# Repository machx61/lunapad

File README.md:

# lunapad
i made this macropad because well my desk was too empty and i needed something(also out of boredom). it can be mainly used to control music and scroll through pages?(or whatever you may like)

# Features:
- 3x3 matrix: 9 keys to handle the best of your tasks
- Rotary encoder: do stuff with just a twist.
- 14 SK6812 Mini LEDs
- QMK firmware

# Renders

# Working:
- It utilises SEEED XIAORP2040 and a custom designed PCB with custom designed 3d printed enclosure and stuff.
- The macropad runs on QMK firmware and the programmed keys can be changed easily using the source files.

# Assembly:
- the case is split into two parts- top and bottom, held together by 4 M3 screws from the underside. there are also 4 M3x3mm heatset inserts on the topside standoffs. the pcb is sandwiched between the parts.

the screwholes can be seen in the image.

# Bill of Materials

| Part | Quantity | Link |
|:-----|--------:|:------|
| Seeed XIAO RP2040 | 1 | [XIAO](https://robocraze.com/products/seeed-studio-xiao-rp2040-development-board?variant=47742255562976&country=IN&currency=INR&utm_medium=product_sync&utm_source=google&utm_content=sag_organic&utm_campaign=sag_organic&campaignid=23145906364&adgroupid=182236965810&keyword=&device=c&gad_source=1&gad_campaignid=23145906364&gbraid=0AAAAADgHQvYtYGwxuRugn9Vvs_5Luixta&gclid=CjwKCAjw2aPVBhBkEiwA0Cptt0xo3sHi-IdjsARB6GH6TKfZ1M9eswIn35SV6bqsJBOXxCKbRXXIgBoC-xAQAvD_BwE)
| MX-style Mechanical Switch | 9 | [switch](https://neomacro.in/products/cherry-mx-switches?srsltid=AfmBOor8tow3bfeM9PI4JXjRf0VAG1diVYeQj8hqUGDjs-gqPkzoR4SC)
| 1N4148 Diode | 9 | [diode](https://www.ktron.in/product/diode-1n4148-th/?srsltid=AfmBOooRQUjsKqpK_EiK3c9zfrjn3DoaM1cKq1ImvCJTQZmOqeq-VMQ6)
| EC11 Rotary Encoder | 1 | [encoder](https://robu.in/product/rotary-encoder-module/)
| SK6812MINI Addressable RGB LED | 9 | [led](https://www.desertcart.in/products/824340559-50-%E5%80%8B-sk6812-mini-e-rgb-2812b-%E3%81%A8%E5%90%8C%E6%A7%98-sk6812-3228?gad_source=1&gad_campaignid=23077216304&gbraid=0AAAAACnLYYvNHCZW8H4DWDfVWvF8gxS9Q&gclid=CjwKCAjw2aPVBhBkEiwA0Cptt4Ja3nVrBJ97lmX0pUguF7jc3NVgRkxuFrKZ9N5f6J9Q7V-lYQpT1RoC440QAvD_BwE)
| Custom PCB | 1 |
| M3 × 3 mm Brass Heat-Set Insert | 4 | [insert](https://onlyscrews.in/products/m3-x-3mm-brass-threaded-inserts?currency=INR&country=IN&variant=49729062273337&stkn=6e84ebfba1b8&utm_source=google&utm_medium=cpc&utm_campaign=googleads_23949204632&utm_id=23949204632&utm_adgroup=&utm_assetgroup=6722775387&utm_content=ad_&utm_term=&utm_matchtype=&utm_device=c&utm_network=x&gad_source=1&gad_campaignid=23953886635&gbraid=0AAAAA9sP2SRjj_2bfcZD9uxIjMuaLaIao&gclid=CjwKCAjw2aPVBhBkEiwA0Cptt7qy5Bg6gMEtFvCYIa8UhckvOcrG2VIVSBWy-0QVkHM6xJ50sQYSwRoCiMsQAvD_BwE)
| M3 × 12 mm Screw | 4 | [screw](https://onlyscrews.in/products/m3-x-12mm-hex-allen-socket-head-high-tensile12-9-black-anodized-screw?currency=INR&country=IN&variant=49862396903737&stkn=6e84ebfba1b8&utm_source=google&utm_medium=cpc&utm_campaign=googleads_22229903987&utm_id=22229903987&utm_adgroup=&utm_assetgroup=6553248255&utm_content=ad_&utm_term=&utm_matchtype=&utm_device=c&utm_network=x&gad_source=1&gad_campaignid=22229905346&gbraid=0AAAAA9sP2SRGRPWr5iqQc1qZ9YGRh8i3g&gclid=CjwKCAjw2aPVBhBkEiwA0CpttxG6n4pTu_Hwbiq8nsTTyXZsGK1pGMrzw8ansKFSEFKX_LcLPL4uwRoC4dcQAvD_BwE)
| MX Keycap | 9 | [keycap](https://keebmaker.com/products/1u-ymdk-mx-keycaps?variant=49717255012651)
| 3D-Printed Encoder Knob | 1 |
| 3D-Printed Case Top | 1 |
| 3D-Printed Case Bottom | 1 |

# Missing Stuff
- VIA support(i intend to roll it out sometime after)
- an OLED screen(if youd want)
- nothing else for a 3x3 macropad

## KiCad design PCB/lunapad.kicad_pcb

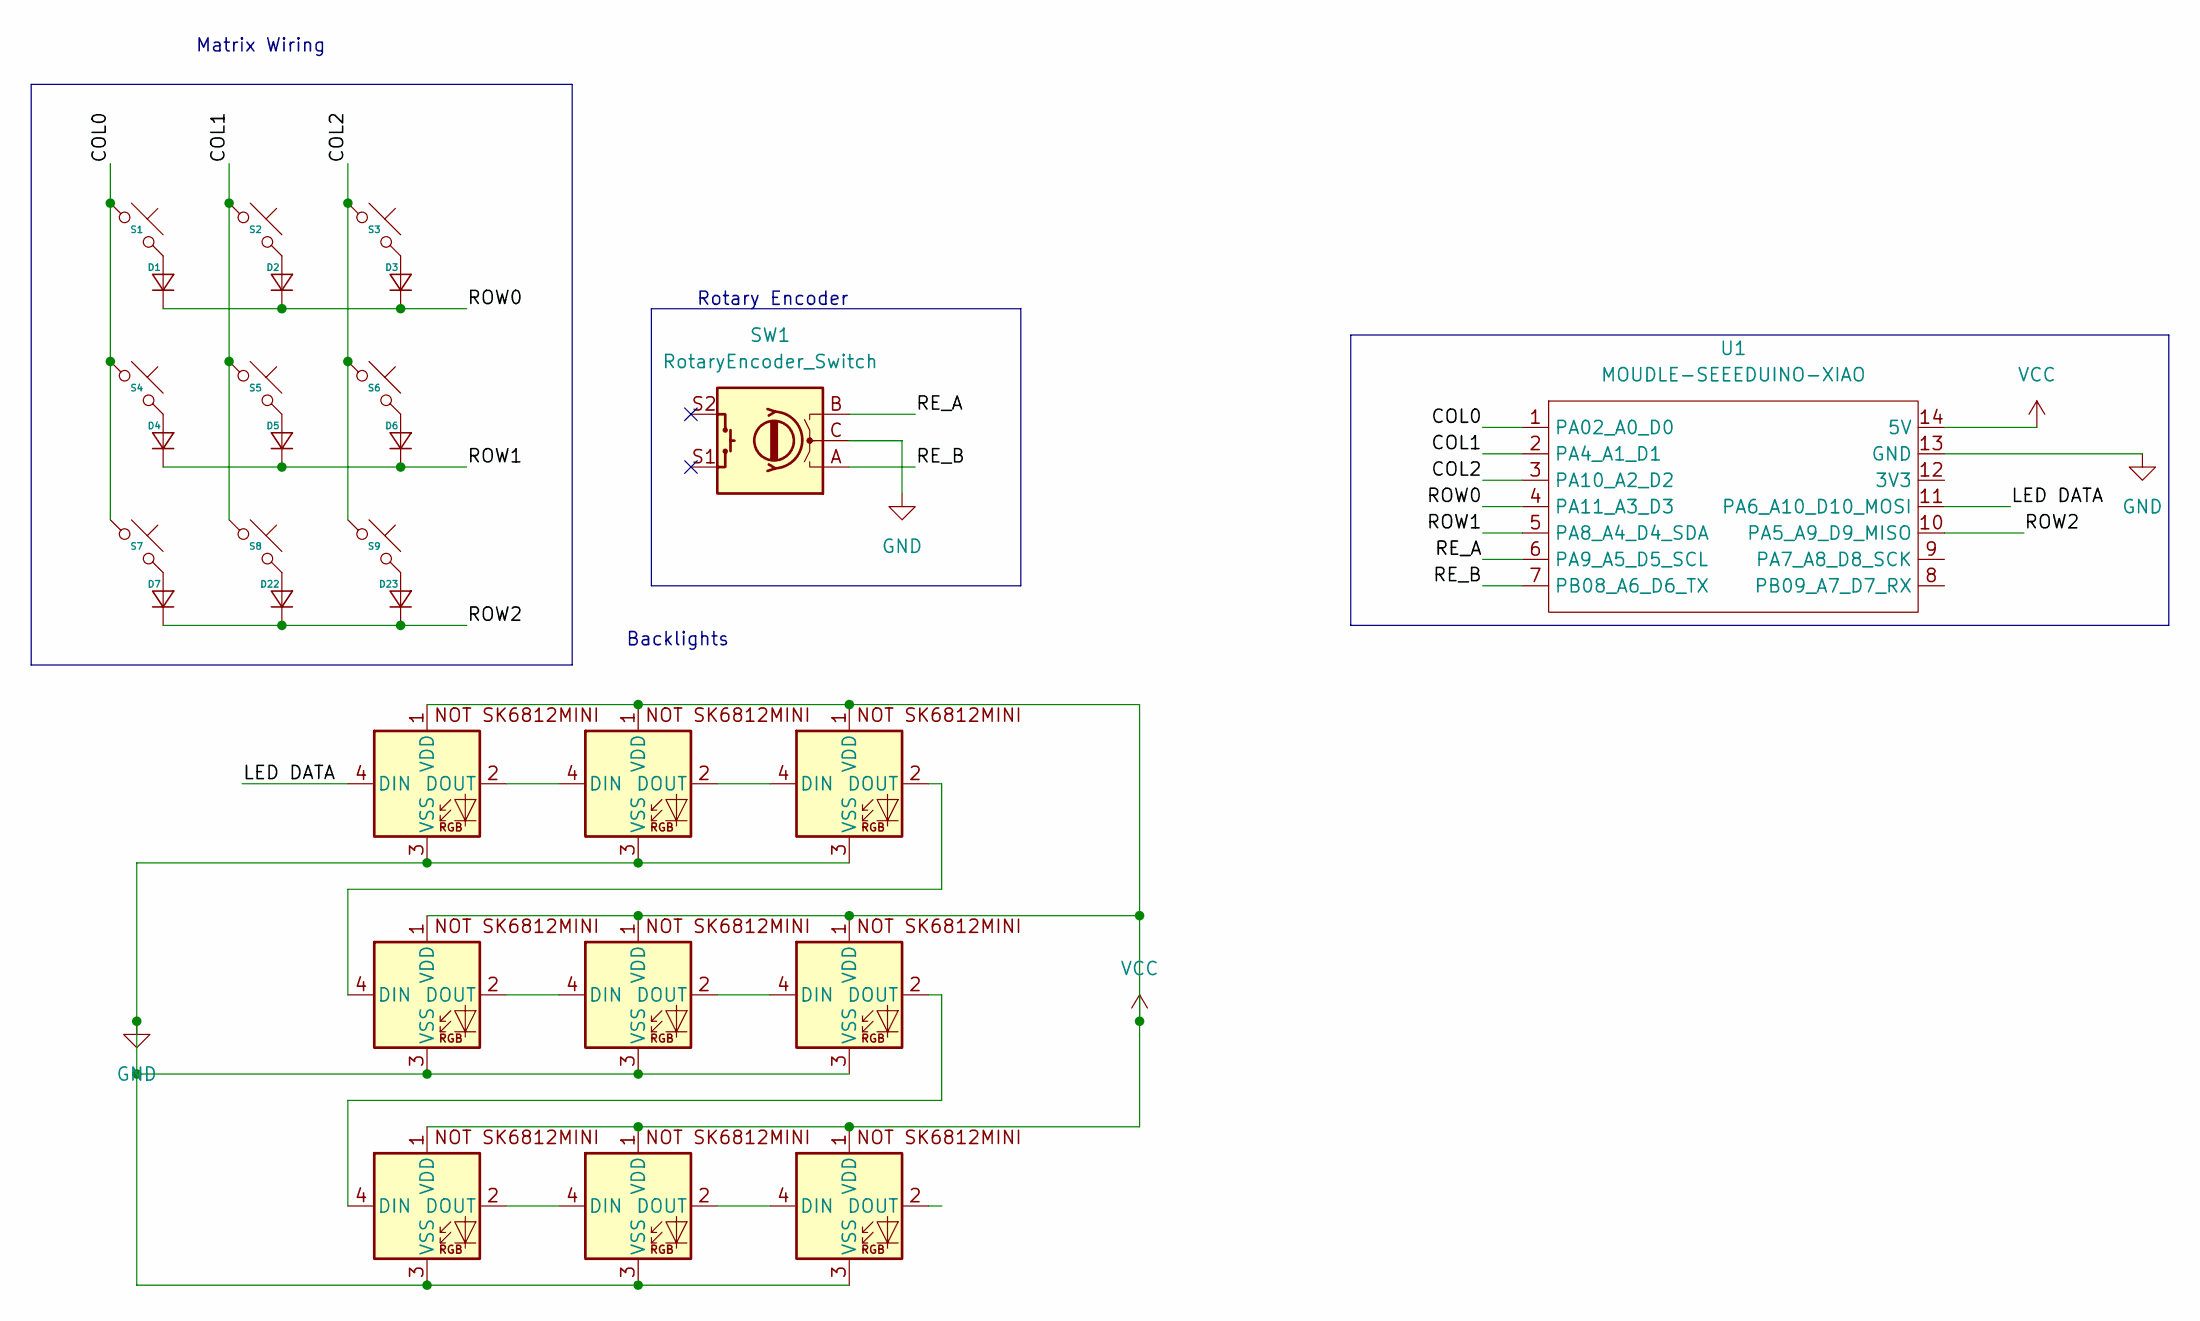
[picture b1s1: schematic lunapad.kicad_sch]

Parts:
D1, D2, D3, D4, D5, D6, D7, D22, D23: Diode_DO-35
D8, D9, D10, D11, D12, D13, D14, D15, D16: SK6812MINI-E; SK6812MINI-E_fixed
S1, S2, S3, S4, S5, S6, S7, S8, S9: MX_PCB_1.00u
SW1: RotaryEncoder_Switch; RotaryEncoder_Alps_EC11E-Switch_Vertical_H20mm
U1: MOUDLE-SEEEDUINO-XIAO; XIAO-Generic-Hybrid-14P-2.54-21X17.8MM

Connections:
/COL0: S1.1, S4.1, S7.1, U1.1 (PA02_A0_D0)
/COL1: S2.1, S5.1, S8.1, U1.2 (PA4_A1_D1)
/COL2: S3.1, S6.1, S9.1, U1.3 (PA10_A2_D2)
/LED DATA: D8.4 (DIN), U1.11 (PA6_A10_D10_MOSI)
/RE_A: SW1.B, U1.6 (PA9_A5_D5_SCL)
/RE_B: SW1.A, U1.7 (PB08_A6_D6_TX)
/ROW0: D1.1 (K), D2.1 (K), D3.1 (K), U1.4 (PA11_A3_D3)
/ROW1: D4.1 (K), D5.1 (K), D6.1 (K), U1.5 (PA8_A4_D4_SDA)
/ROW2: D7.1 (K), D22.1 (K), D23.1 (K), U1.10 (PA5_A9_D9_MISO)
GND: D8.3 (VSS), D9.3 (VSS), D10.3 (VSS), D11.3 (VSS), D12.3 (VSS), D13.3 (VSS), D14.3 (VSS), D15.3 (VSS), D16.3 (VSS), SW1.C, U1.13 (GND)
unnamed: D1.2 (A), S1.2
unnamed: D2.2 (A), S2.2
unnamed: D3.2 (A), S3.2
unnamed: D4.2 (A), S4.2
unnamed: D5.2 (A), S5.2
unnamed: D6.2 (A), S6.2
unnamed: D7.2 (A), S7.2
unnamed: D8.2 (DOUT), D9.4 (DIN)
unnamed: D9.2 (DOUT), D10.4 (DIN)
unnamed: D10.2 (DOUT), D11.4 (DIN)
unnamed: D11.2 (DOUT), D12.4 (DIN)
unnamed: D12.2 (DOUT), D13.4 (DIN)
unnamed: D13.2 (DOUT), D14.4 (DIN)
unnamed: D14.2 (DOUT), D15.4 (DIN)
unnamed: D15.2 (DOUT), D16.4 (DIN)
unnamed: D22.2 (A), S8.2
unnamed: D23.2 (A), S9.2
VCC: D8.1 (VDD), D9.1 (VDD), D10.1 (VDD), D11.1 (VDD), D12.1 (VDD), D13.1 (VDD), D14.1 (VDD), D15.1 (VDD), D16.1 (VDD), U1.14 (5V)

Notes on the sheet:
Rotary Encoder
Backlights
Matrix Wiring

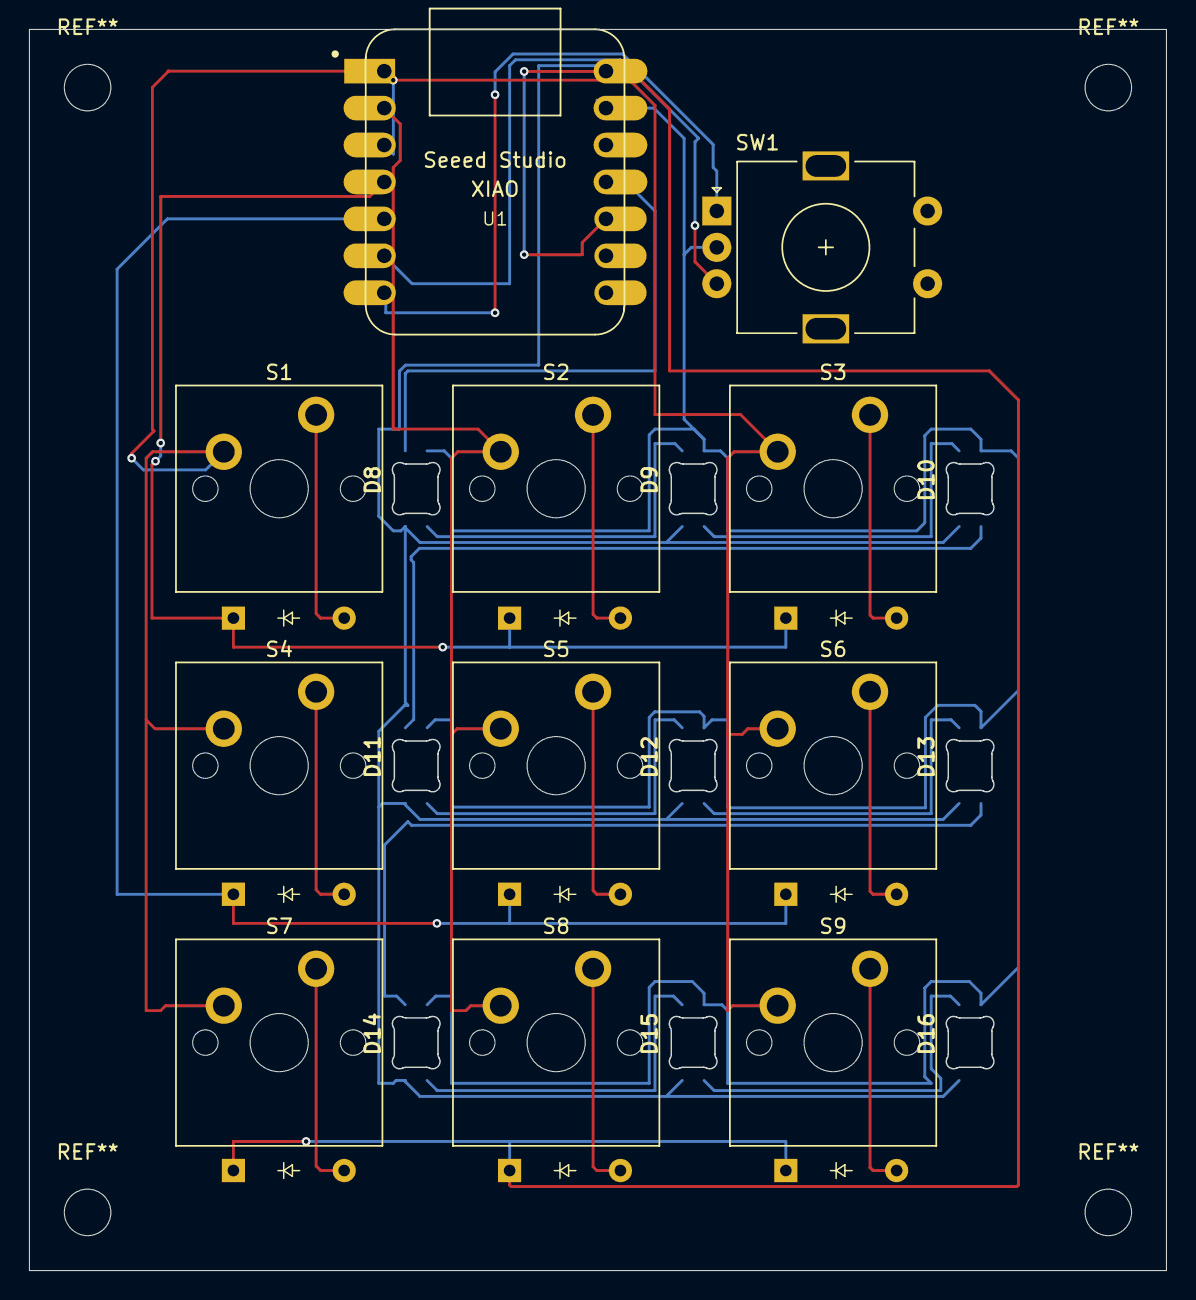
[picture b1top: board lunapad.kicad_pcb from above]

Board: 2 copper layers, 78.2 x 85.4 mm, 29 parts (0 on the bottom side), 28 nets.
